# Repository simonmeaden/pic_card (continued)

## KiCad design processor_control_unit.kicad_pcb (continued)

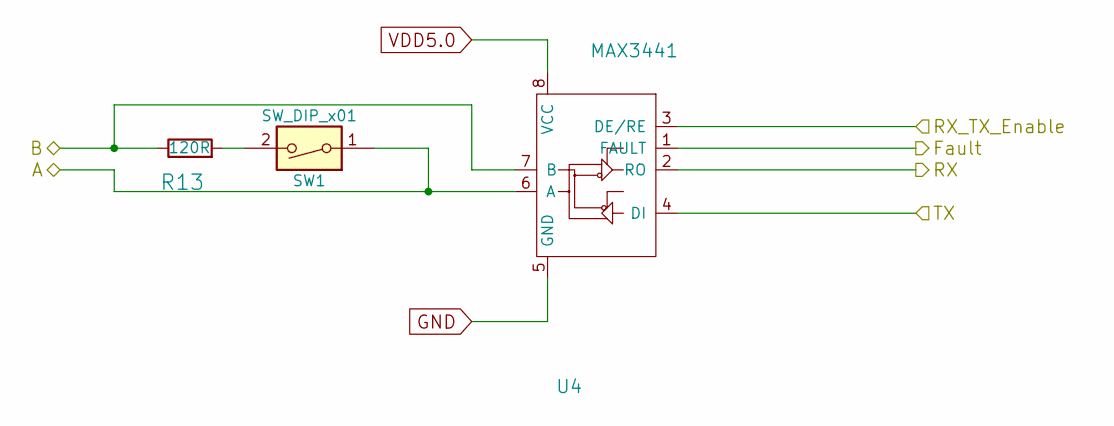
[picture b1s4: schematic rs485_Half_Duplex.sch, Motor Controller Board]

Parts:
R13: 120R; R_0805_2012Metric
SW1: SW_DIP_x01; OMRON_A6S-110X-H_1xSPST
U4: MAX3441; SO-8

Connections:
/Processor Control Unit/485-FAULT: U4.1 (FAULT); also elsewhere on the board
/Processor Control Unit/485-RX: U4.2 (RO); also elsewhere on the board
/Processor Control Unit/485-RX_TX_Enable: U4.3 (DE/RE); also elsewhere on the board
/Processor Control Unit/485-TX: U4.4 (DI); also elsewhere on the board
/RS485_N: SW1.1, U4.6 (A); also elsewhere on the board
/RS485_P: R13.1, U4.7 (B); also elsewhere on the board
GND: U4.5 (GND); also elsewhere on the board
unnamed: R13.2, SW1.2
VDD5.0: U4.8 (VCC); also elsewhere on the board

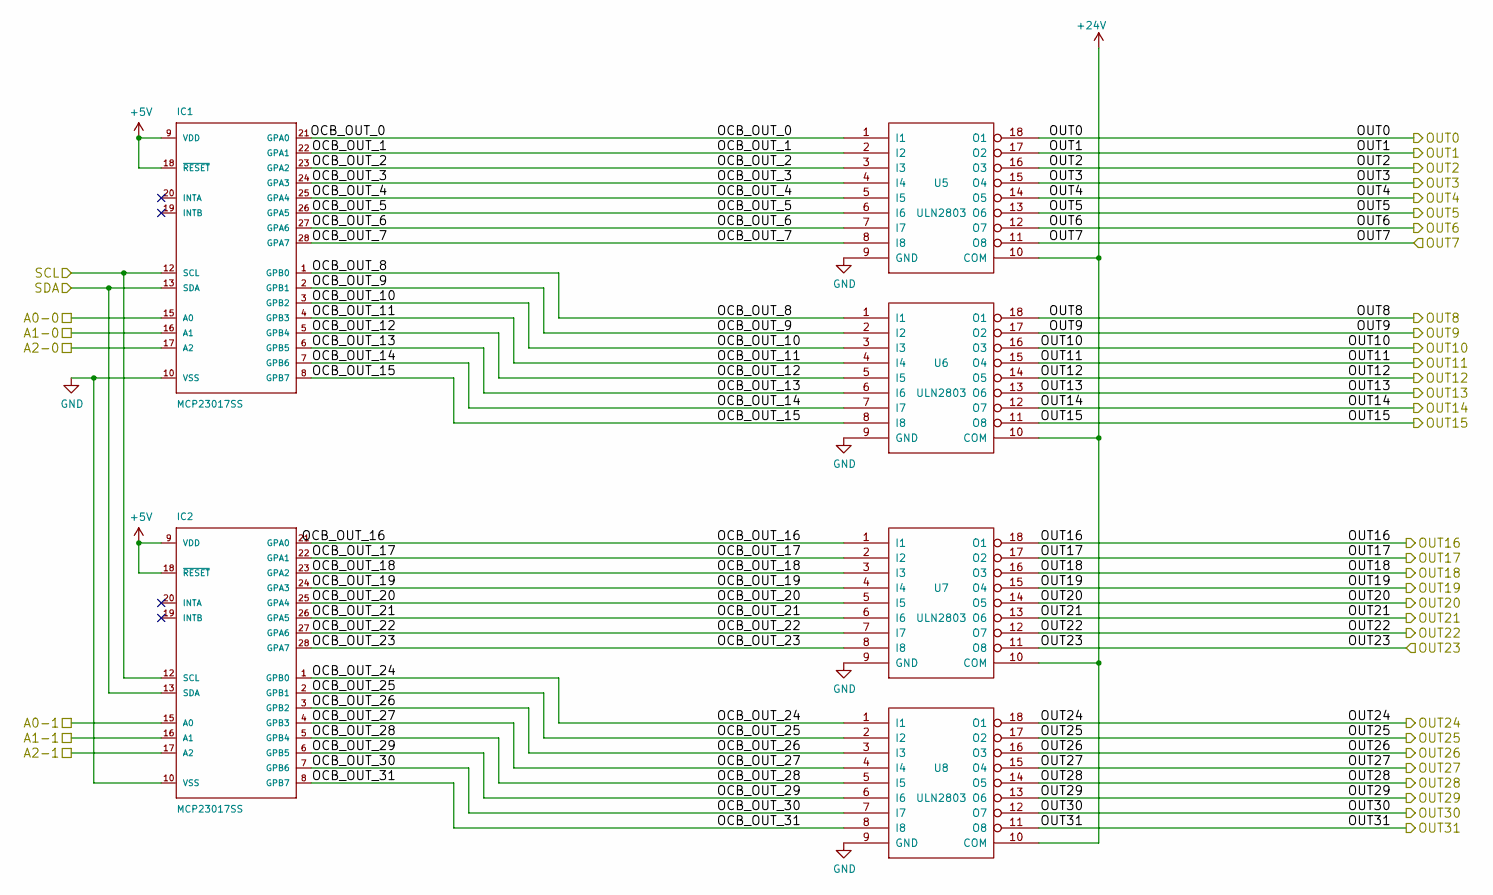
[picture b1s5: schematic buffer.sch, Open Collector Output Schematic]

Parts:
IC1, IC2: MCP23017SS; SSOP28
U5, U6, U7, U8: ULN2803; SOIC-18W_7.5x11.6mm_Pitch1.27mm

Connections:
+5V: IC1.9 (VDD), IC1.15 (A0), IC1.17 (A2), IC1.18 (~RESET), IC2.9 (VDD), IC2.16 (A1), IC2.17 (A2), IC2.18 (~RESET); also elsewhere on the board
+24V: U5.10 (COM), U6.10 (COM), U7.10 (COM), U8.10 (COM); also elsewhere on the board
/OUT-1: U5.18 (O1); also elsewhere on the board
/OUT-2: U5.17 (O2); also elsewhere on the board
/OUT-3: U5.16 (O3); also elsewhere on the board
/OUT-4: U5.15 (O4); also elsewhere on the board
/OUT-5: U5.14 (O5); also elsewhere on the board
/OUT-6: U5.13 (O6); also elsewhere on the board
/OUT-7: U5.12 (O7); also elsewhere on the board
/OUT-8: U5.11 (O8); also elsewhere on the board
/OUT-9: U6.18 (O1); also elsewhere on the board
/OUT-10: U6.17 (O2); also elsewhere on the board
/OUT-11: U6.16 (O3); also elsewhere on the board
/OUT-12: U6.15 (O4); also elsewhere on the board
/OUT-13: U6.14 (O5); also elsewhere on the board
/OUT-14: U6.13 (O6); also elsewhere on the board
/OUT-15: U6.12 (O7); also elsewhere on the board
/OUT-16: U6.11 (O8); also elsewhere on the board
/OUT-17: U7.18 (O1); also elsewhere on the board
/OUT-18: U7.17 (O2); also elsewhere on the board
/OUT-19: U7.16 (O3); also elsewhere on the board
/OUT-20: U7.15 (O4); also elsewhere on the board
/OUT-21: U7.14 (O5); also elsewhere on the board
/OUT-22: U7.13 (O6); also elsewhere on the board
/OUT-23: U7.12 (O7); also elsewhere on the board
/OUT-24: U7.11 (O8); also elsewhere on the board
/OUT-25: U8.18 (O1); also elsewhere on the board
/OUT-26: U8.17 (O2); also elsewhere on the board
/OUT-27: U8.16 (O3); also elsewhere on the board
/OUT-28: U8.15 (O4); also elsewhere on the board
/OUT-29: U8.14 (O5); also elsewhere on the board
/OUT-30: U8.13 (O6); also elsewhere on the board
/OUT-31: U8.12 (O7); also elsewhere on the board
/OUT-32: U8.11 (O8); also elsewhere on the board
/Open Collector Buffered Outputs/OCB_OUT_0: IC1.21 (GPA0), U5.1 (I1)
/Open Collector Buffered Outputs/OCB_OUT_1: IC1.22 (GPA1), U5.2 (I2)
/Open Collector Buffered Outputs/OCB_OUT_2: IC1.23 (GPA2), U5.3 (I3)
/Open Collector Buffered Outputs/OCB_OUT_3: IC1.24 (GPA3), U5.4 (I4)
/Open Collector Buffered Outputs/OCB_OUT_4: IC1.25 (GPA4), U5.5 (I5)
/Open Collector Buffered Outputs/OCB_OUT_5: IC1.26 (GPA5), U5.6 (I6)
/Open Collector Buffered Outputs/OCB_OUT_6: IC1.27 (GPA6), U5.7 (I7)
/Open Collector Buffered Outputs/OCB_OUT_7: IC1.28 (GPA7), U5.8 (I8)
/Open Collector Buffered Outputs/OCB_OUT_8: IC1.1 (GPB0), U6.1 (I1)
/Open Collector Buffered Outputs/OCB_OUT_9: IC1.2 (GPB1), U6.2 (I2)
/Open Collector Buffered Outputs/OCB_OUT_10: IC1.3 (GPB2), U6.3 (I3)
/Open Collector Buffered Outputs/OCB_OUT_11: IC1.4 (GPB3), U6.4 (I4)
/Open Collector Buffered Outputs/OCB_OUT_12: IC1.5 (GPB4), U6.5 (I5)
/Open Collector Buffered Outputs/OCB_OUT_13: IC1.6 (GPB5), U6.6 (I6)
/Open Collector Buffered Outputs/OCB_OUT_14: IC1.7 (GPB6), U6.7 (I7)
/Open Collector Buffered Outputs/OCB_OUT_15: IC1.8 (GPB7), U6.8 (I8)
/Open Collector Buffered Outputs/OCB_OUT_16: IC2.21 (GPA0), U7.1 (I1)
/Open Collector Buffered Outputs/OCB_OUT_17: IC2.22 (GPA1), U7.2 (I2)
/Open Collector Buffered Outputs/OCB_OUT_18: IC2.23 (GPA2), U7.3 (I3)
/Open Collector Buffered Outputs/OCB_OUT_19: IC2.24 (GPA3), U7.4 (I4)
/Open Collector Buffered Outputs/OCB_OUT_20: IC2.25 (GPA4), U7.5 (I5)
/Open Collector Buffered Outputs/OCB_OUT_21: IC2.26 (GPA5), U7.6 (I6)
/Open Collector Buffered Outputs/OCB_OUT_22: IC2.27 (GPA6), U7.7 (I7)
/Open Collector Buffered Outputs/OCB_OUT_23: IC2.28 (GPA7), U7.8 (I8)
/Open Collector Buffered Outputs/OCB_OUT_24: IC2.1 (GPB0), U8.1 (I1)
/Open Collector Buffered Outputs/OCB_OUT_25: IC2.2 (GPB1), U8.2 (I2)
/Open Collector Buffered Outputs/OCB_OUT_26: IC2.3 (GPB2), U8.3 (I3)
/Open Collector Buffered Outputs/OCB_OUT_27: IC2.4 (GPB3), U8.4 (I4)
/Open Collector Buffered Outputs/OCB_OUT_28: IC2.5 (GPB4), U8.5 (I5)
/Open Collector Buffered Outputs/OCB_OUT_29: IC2.6 (GPB5), U8.6 (I6)
/Open Collector Buffered Outputs/OCB_OUT_30: IC2.7 (GPB6), U8.7 (I7)
/Open Collector Buffered Outputs/OCB_OUT_31: IC2.8 (GPB7), U8.8 (I8)
/Open Collector Buffered Outputs/SCL: IC1.12 (SCL), IC2.12 (SCL); also elsewhere on the board
/Open Collector Buffered Outputs/SDA: IC1.13 (SDA), IC2.13 (SDA); also elsewhere on the board
GND: IC1.10 (VSS), IC1.16 (A1), IC2.10 (VSS), IC2.15 (A0), U5.9 (GND), U6.9 (GND), U7.9 (GND), U8.9 (GND); also elsewhere on the board

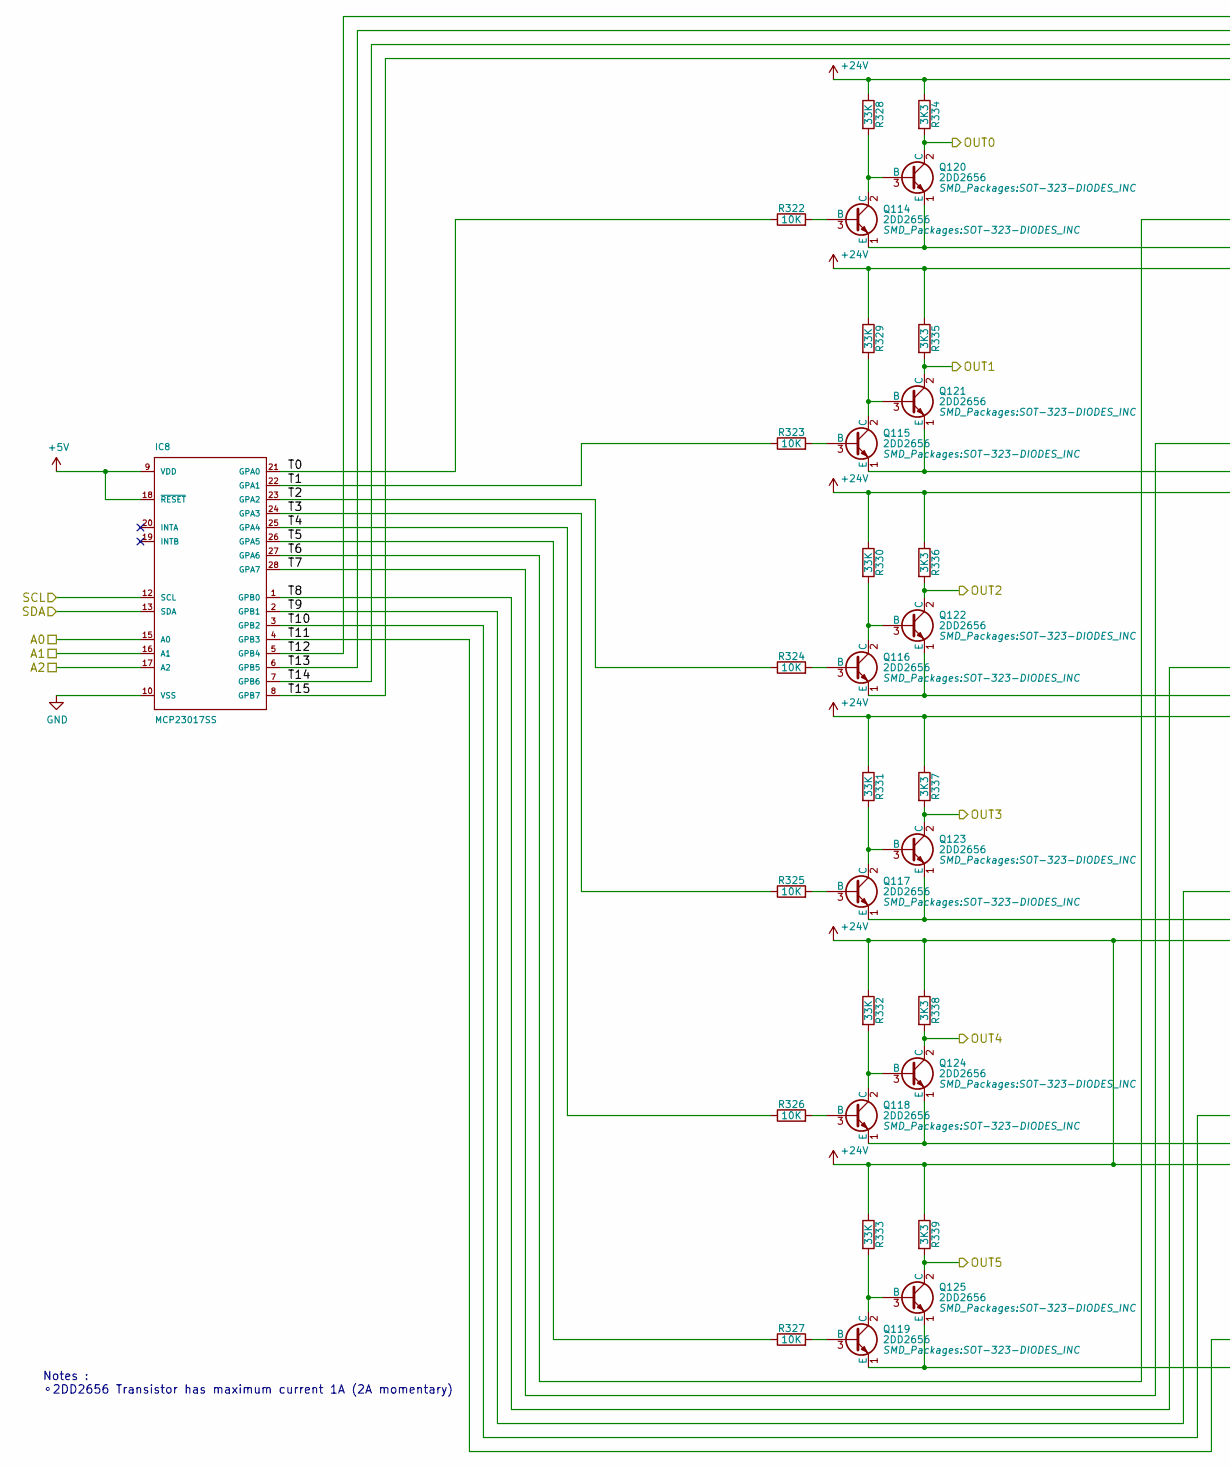
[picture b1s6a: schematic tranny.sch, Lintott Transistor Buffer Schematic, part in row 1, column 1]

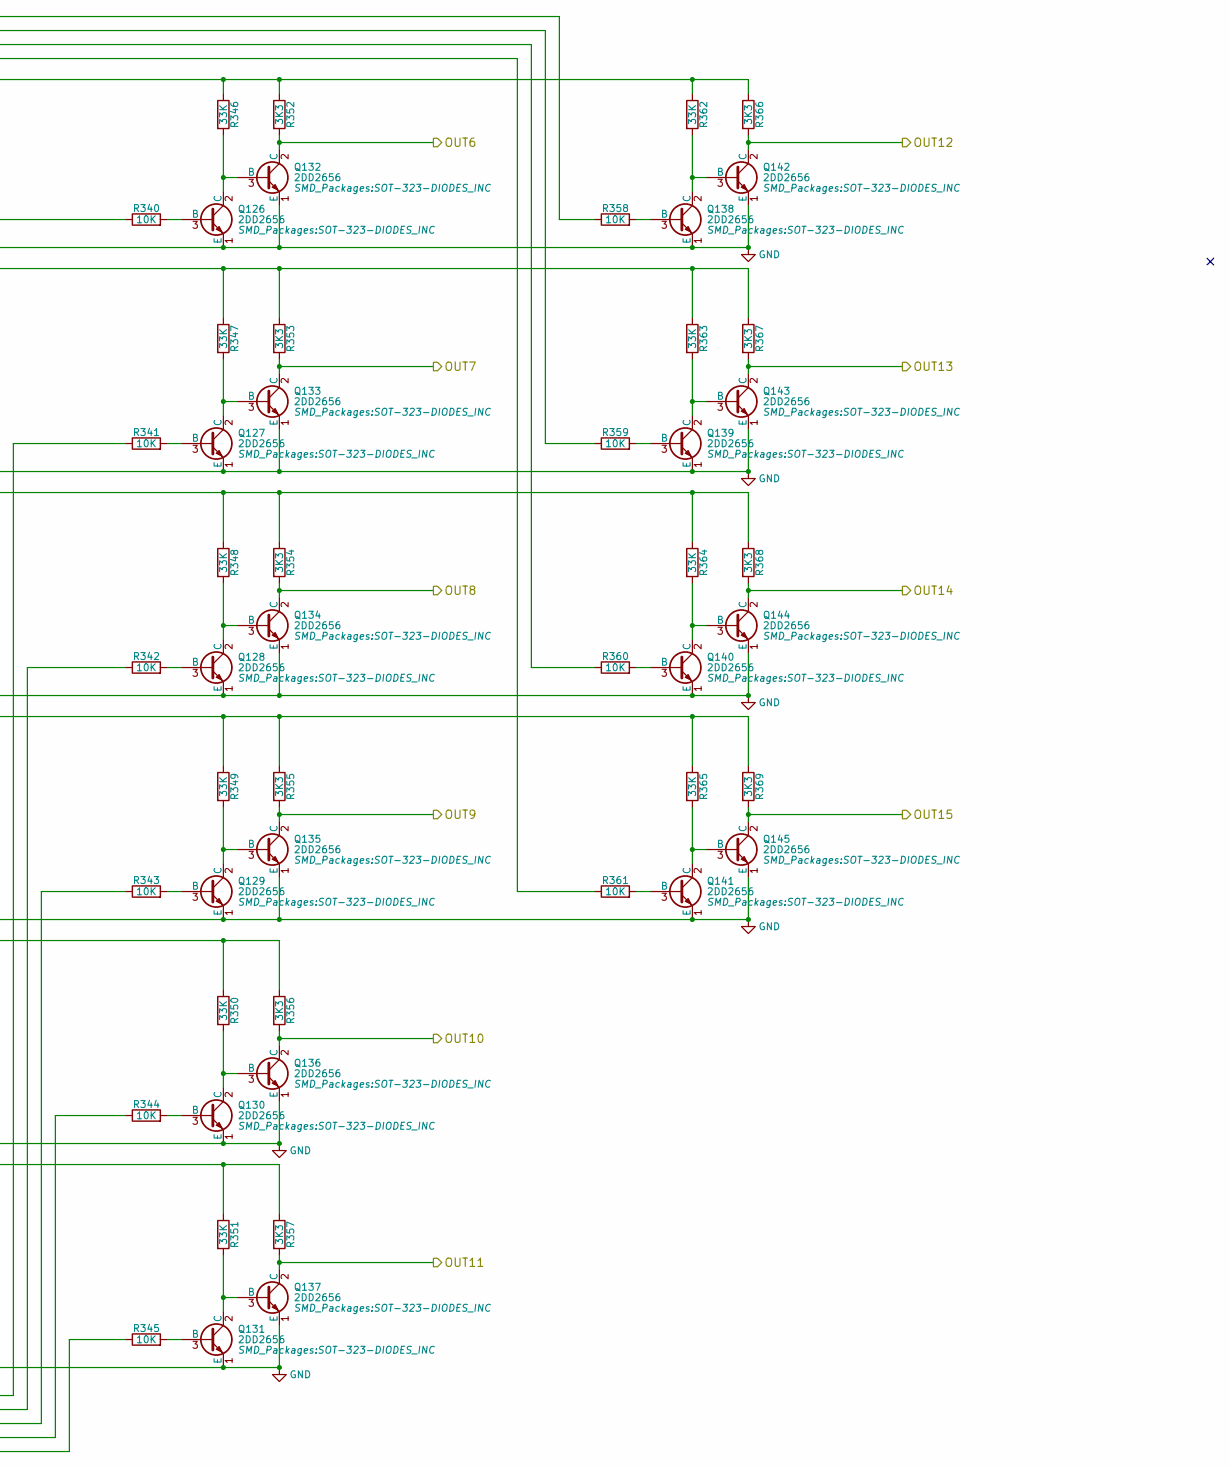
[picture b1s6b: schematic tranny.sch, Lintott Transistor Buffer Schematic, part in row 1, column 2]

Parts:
IC3: MCP23017SS; SSOP28
Q1, Q2, Q3, Q4, Q5, Q6, Q7, Q8, Q9, Q10, Q11, Q12, Q13, Q14, Q15, Q16, Q17, Q18, Q19, Q20, Q21, Q22, Q23, Q24, Q25, Q26, Q27, Q28, Q29, Q30, Q31, Q32: 2DD2656; SOT-323-DIODES_INC
R14, R15, R16, R17, R18, R19, R32, R33, R34, R35, R36, R37, R50, R51, R52, R53: 10K; R_0805_2012Metric
R20, R21, R22, R23, R24, R25, R38, R39, R40, R41, R42, R43, R54, R55, R56, R57: 33K; R_0805_2012Metric
R26, R27, R28, R29, R30, R31, R44, R45, R46, R47, R48, R49, R58, R59, R60, R61: 3K3; R_0805_2012Metric

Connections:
+5V: IC3.9 (VDD), IC3.17 (A2), IC3.18 (~RESET); also elsewhere on the board
+24V: R20.1, R21.1, R22.1, R23.1, R24.1, R25.1, R26.1, R27.1, R28.1, R29.1, R30.1, R31.1, R38.1, R39.1, R40.1, R41.1, R42.1, R43.1, R44.1, R45.1, R46.1, R47.1, R48.1, R49.1, R54.1, R55.1, R56.1, R57.1, R58.1, R59.1, R60.1, R61.1; also elsewhere on the board
/OUT-33: Q7.2 (C), R26.2; also elsewhere on the board
/OUT-34: Q8.2 (C), R27.2; also elsewhere on the board
/OUT-35: Q9.2 (C), R28.2; also elsewhere on the board
/OUT-36: Q10.2 (C), R29.2; also elsewhere on the board
/OUT-37: Q11.2 (C), R30.2; also elsewhere on the board
/OUT-38: Q12.2 (C), R31.2; also elsewhere on the board
/OUT-39: Q19.2 (C), R44.2; also elsewhere on the board
/OUT-40: Q20.2 (C), R45.2; also elsewhere on the board
/OUT-41: Q21.2 (C), R46.2; also elsewhere on the board
/OUT-42: Q22.2 (C), R47.2; also elsewhere on the board
/OUT-43: Q23.2 (C), R48.2; also elsewhere on the board
/OUT-44: Q24.2 (C), R49.2; also elsewhere on the board
/OUT-45: Q29.2 (C), R58.2; also elsewhere on the board
/OUT-46: Q30.2 (C), R59.2; also elsewhere on the board
/OUT-47: Q31.2 (C), R60.2; also elsewhere on the board
/OUT-48: Q32.2 (C), R61.2; also elsewhere on the board
/Open Collector Buffered Outputs/SCL: IC3.12 (SCL); also elsewhere on the board
/Open Collector Buffered Outputs/SDA: IC3.13 (SDA); also elsewhere on the board
/Transistor buffered output 1/T0: IC3.21 (GPA0), R14.1
/Transistor buffered output 1/T1: IC3.22 (GPA1), R15.1
/Transistor buffered output 1/T2: IC3.23 (GPA2), R16.1
/Transistor buffered output 1/T3: IC3.24 (GPA3), R17.1
/Transistor buffered output 1/T4: IC3.25 (GPA4), R18.1
/Transistor buffered output 1/T5: IC3.26 (GPA5), R19.1
/Transistor buffered output 1/T6: IC3.27 (GPA6), R32.1
/Transistor buffered output 1/T7: IC3.28 (GPA7), R33.1
/Transistor buffered output 1/T8: IC3.1 (GPB0), R34.1
/Transistor buffered output 1/T9: IC3.2 (GPB1), R35.1
/Transistor buffered output 1/T10: IC3.3 (GPB2), R36.1
/Transistor buffered output 1/T11: IC3.4 (GPB3), R37.1
/Transistor buffered output 1/T12: IC3.5 (GPB4), R50.1
/Transistor buffered output 1/T13: IC3.6 (GPB5), R51.1
/Transistor buffered output 1/T14: IC3.7 (GPB6), R52.1
/Transistor buffered output 1/T15: IC3.8 (GPB7), R53.1
GND: IC3.10 (VSS), IC3.15 (A0), IC3.16 (A1), Q1.1 (E), Q2.1 (E), Q3.1 (E), Q4.1 (E), Q5.1 (E), Q6.1 (E), Q7.1 (E), Q8.1 (E), Q9.1 (E), Q10.1 (E), Q11.1 (E), Q12.1 (E), Q13.1 (E), Q14.1 (E), Q15.1 (E), Q16.1 (E), Q17.1 (E), Q18.1 (E), Q19.1 (E), Q20.1 (E), Q21.1 (E), Q22.1 (E), Q23.1 (E), Q24.1 (E), Q25.1 (E), Q26.1 (E), Q27.1 (E), Q28.1 (E), Q29.1 (E), Q30.1 (E), Q31.1 (E), Q32.1 (E); also elsewhere on the board
unnamed: Q1.2 (C), Q7.3 (B), R20.2
unnamed: Q1.3 (B), R14.2
unnamed: Q2.2 (C), Q8.3 (B), R21.2
unnamed: Q2.3 (B), R15.2
unnamed: Q3.2 (C), Q9.3 (B), R22.2
unnamed: Q3.3 (B), R16.2
unnamed: Q4.3 (B), R17.2
unnamed: Q5.3 (B), R18.2
unnamed: Q6.3 (B), R19.2
unnamed: Q4.2 (C), Q10.3 (B), R23.2
unnamed: Q5.2 (C), Q11.3 (B), R24.2
unnamed: Q6.2 (C), Q12.3 (B), R25.2
unnamed: Q13.2 (C), Q19.3 (B), R38.2
unnamed: Q13.3 (B), R32.2
unnamed: Q14.2 (C), Q20.3 (B), R39.2
unnamed: Q14.3 (B), R33.2
unnamed: Q15.2 (C), Q21.3 (B), R40.2
unnamed: Q15.3 (B), R34.2
unnamed: Q16.2 (C), Q22.3 (B), R41.2
unnamed: Q16.3 (B), R35.2
unnamed: Q17.2 (C), Q23.3 (B), R42.2
unnamed: Q17.3 (B), R36.2
unnamed: Q18.2 (C), Q24.3 (B), R43.2
unnamed: Q18.3 (B), R37.2
unnamed: Q25.2 (C), Q29.3 (B), R54.2
unnamed: Q25.3 (B), R50.2
unnamed: Q26.2 (C), Q30.3 (B), R55.2
unnamed: Q26.3 (B), R51.2
unnamed: Q27.2 (C), Q31.3 (B), R56.2
unnamed: Q27.3 (B), R52.2
unnamed: Q28.2 (C), Q32.3 (B), R57.2
unnamed: Q28.3 (B), R53.2

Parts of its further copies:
IC8: MCP23017SS; SSOP28
Q114, Q115, Q116, Q117, Q118, Q119, Q120, Q121, Q122, Q123, Q124, Q125, Q126, Q127, Q128, Q129, Q130, Q131, Q132, Q133, Q134, Q135, Q136, Q137, Q138, Q139, Q140, Q141, Q142, Q143, Q144, Q145: 2DD2656; SOT-323-DIODES_INC
R322, R323, R324, R325, R326, R327, R340, R341, R342, R343, R344, R345, R358, R359, R360, R361: 10K; R_0805_2012Metric
R328, R329, R330, R331, R332, R333, R346, R347, R348, R349, R350, R351, R362, R363, R364, R365: 33K; R_0805_2012Metric
R334, R335, R336, R337, R338, R339, R352, R353, R354, R355, R356, R357, R366, R367, R368, R369: 3K3; R_0805_2012Metric

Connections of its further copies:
+5V: IC8.9 (VDD), IC8.15 (A0), IC8.16 (A1), IC8.17 (A2), IC8.18 (~RESET); also elsewhere on the board
+24V: R328.1, R329.1, R330.1, R331.1, R332.1, R333.1, R334.1, R335.1, R336.1, R337.1, R338.1, R339.1, R346.1, R347.1, R348.1, R349.1, R350.1, R351.1, R352.1, R353.1, R354.1, R355.1, R356.1, R357.1, R362.1, R363.1, R364.1, R365.1, R366.1, R367.1, R368.1, R369.1; also elsewhere on the board
/OUT-49: Q120.2 (C), R334.2; also elsewhere on the board
/OUT-50: Q121.2 (C), R335.2; also elsewhere on the board
/OUT-51: Q122.2 (C), R336.2; also elsewhere on the board
/OUT-52: Q123.2 (C), R337.2; also elsewhere on the board
/OUT-53: Q124.2 (C), R338.2; also elsewhere on the board
/OUT-54: Q125.2 (C), R339.2; also elsewhere on the board
/OUT-55: Q132.2 (C), R352.2; also elsewhere on the board
/OUT-56: Q133.2 (C), R353.2; also elsewhere on the board
/OUT-57: Q134.2 (C), R354.2; also elsewhere on the board
/OUT-58: Q135.2 (C), R355.2; also elsewhere on the board
/OUT-59: Q136.2 (C), R356.2; also elsewhere on the board
/OUT-60: Q137.2 (C), R357.2; also elsewhere on the board
/OUT-61: Q142.2 (C), R366.2; also elsewhere on the board
/OUT-62: Q143.2 (C), R367.2; also elsewhere on the board
/OUT-63: Q144.2 (C), R368.2; also elsewhere on the board
/OUT-64: Q145.2 (C), R369.2; also elsewhere on the board
/Open Collector Buffered Outputs/SCL: IC8.12 (SCL); also elsewhere on the board
/Open Collector Buffered Outputs/SDA: IC8.13 (SDA); also elsewhere on the board
/Transistor buffered output 2/T0: IC8.21 (GPA0), R322.1
/Transistor buffered output 2/T1: IC8.22 (GPA1), R323.1
/Transistor buffered output 2/T2: IC8.23 (GPA2), R324.1
/Transistor buffered output 2/T3: IC8.24 (GPA3), R325.1
/Transistor buffered output 2/T4: IC8.25 (GPA4), R326.1
/Transistor buffered output 2/T5: IC8.26 (GPA5), R327.1
/Transistor buffered output 2/T6: IC8.27 (GPA6), R340.1
/Transistor buffered output 2/T7: IC8.28 (GPA7), R341.1
/Transistor buffered output 2/T8: IC8.1 (GPB0), R342.1
/Transistor buffered output 2/T9: IC8.2 (GPB1), R343.1
/Transistor buffered output 2/T10: IC8.3 (GPB2), R344.1
/Transistor buffered output 2/T11: IC8.4 (GPB3), R345.1
/Transistor buffered output 2/T12: IC8.5 (GPB4), R358.1
/Transistor buffered output 2/T13: IC8.6 (GPB5), R359.1
/Transistor buffered output 2/T14: IC8.7 (GPB6), R360.1
/Transistor buffered output 2/T15: IC8.8 (GPB7), R361.1
GND: IC8.10 (VSS), Q114.1 (E), Q115.1 (E), Q116.1 (E), Q117.1 (E), Q118.1 (E), Q119.1 (E), Q120.1 (E), Q121.1 (E), Q122.1 (E), Q123.1 (E), Q124.1 (E), Q125.1 (E), Q126.1 (E), Q127.1 (E), Q128.1 (E), Q129.1 (E), Q130.1 (E), Q131.1 (E), Q132.1 (E), Q133.1 (E), Q134.1 (E), Q135.1 (E), Q136.1 (E), Q137.1 (E), Q138.1 (E), Q139.1 (E), Q140.1 (E), Q141.1 (E), Q142.1 (E), Q143.1 (E), Q144.1 (E), Q145.1 (E); also elsewhere on the board
unnamed: Q114.2 (C), Q120.3 (B), R328.2
unnamed: Q114.3 (B), R322.2
unnamed: Q115.2 (C), Q121.3 (B), R329.2
unnamed: Q115.3 (B), R323.2
unnamed: Q116.2 (C), Q122.3 (B), R330.2
unnamed: Q116.3 (B), R324.2
unnamed: Q117.2 (C), Q123.3 (B), R331.2
unnamed: Q117.3 (B), R325.2
unnamed: Q118.2 (C), Q124.3 (B), R332.2
unnamed: Q118.3 (B), R326.2
unnamed: Q119.2 (C), Q125.3 (B), R333.2
unnamed: Q119.3 (B), R327.2
unnamed: Q126.2 (C), Q132.3 (B), R346.2
unnamed: Q126.3 (B), R340.2
unnamed: Q127.2 (C), Q133.3 (B), R347.2
unnamed: Q127.3 (B), R341.2
unnamed: Q128.2 (C), Q134.3 (B), R348.2
unnamed: Q128.3 (B), R342.2
unnamed: Q129.2 (C), Q135.3 (B), R349.2
unnamed: Q129.3 (B), R343.2
unnamed: Q130.2 (C), Q136.3 (B), R350.2
unnamed: Q130.3 (B), R344.2
unnamed: Q131.2 (C), Q137.3 (B), R351.2
unnamed: Q131.3 (B), R345.2
unnamed: Q138.2 (C), Q142.3 (B), R362.2
unnamed: Q138.3 (B), R358.2
unnamed: Q139.2 (C), Q143.3 (B), R363.2
unnamed: Q139.3 (B), R359.2
unnamed: Q140.2 (C), Q144.3 (B), R364.2
unnamed: Q140.3 (B), R360.2
unnamed: Q141.2 (C), Q145.3 (B), R365.2
unnamed: Q141.3 (B), R361.2

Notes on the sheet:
Notes : ⚬2DD2656 Transistor has maximum current 1A (2A momentary)
